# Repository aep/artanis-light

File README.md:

vehicle gps tracker with battery
================================

- cpu:     ESP32
- modem:   Quectel BG96 minipcie
- supply:  ~12V from vehicle
- battery: 2 14500 lifepo cells at 6.4V

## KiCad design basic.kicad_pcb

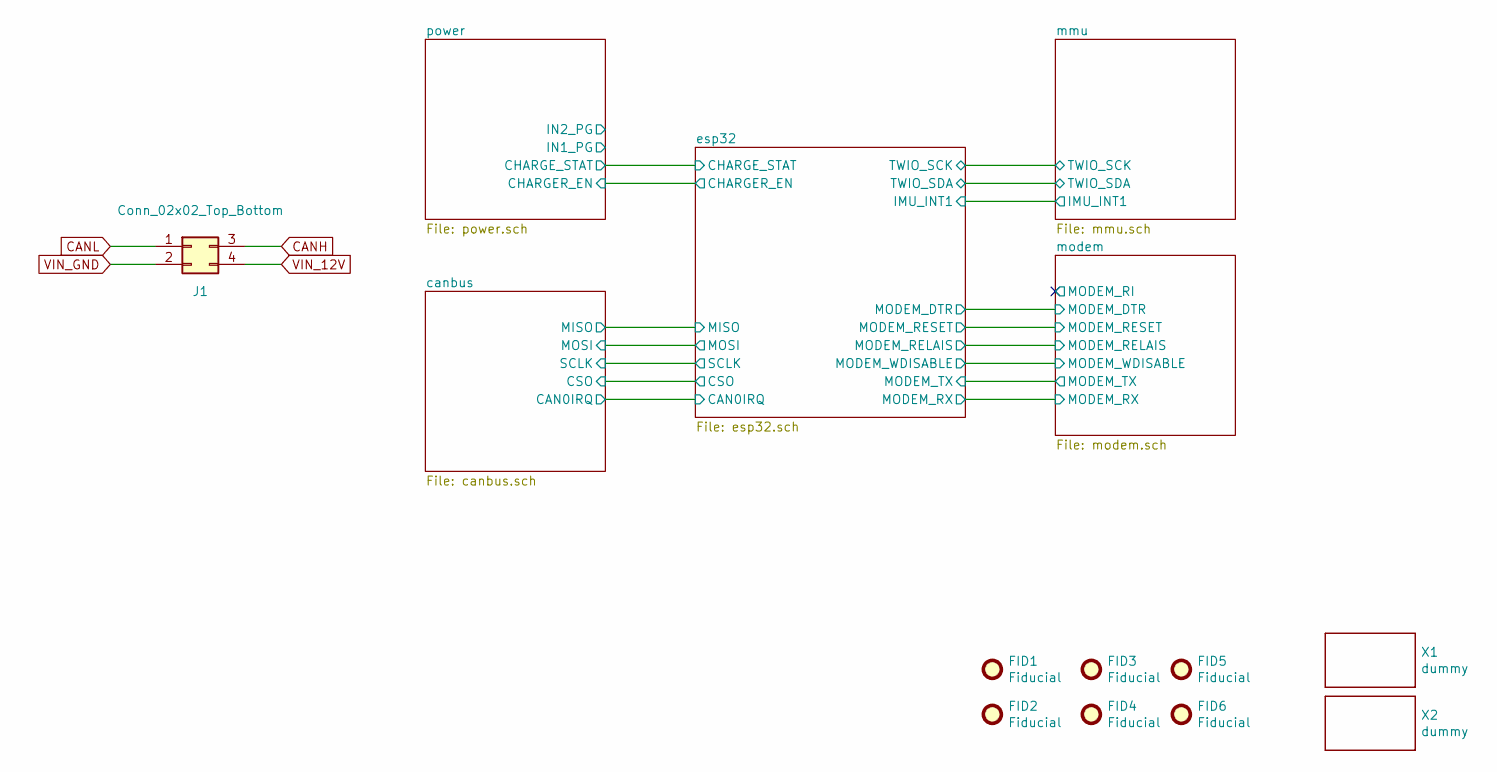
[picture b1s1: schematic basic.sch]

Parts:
FID1, FID2, FID3, FID4, FID5, FID6: Fiducial; FIDUCIAL-1X2
J1: Conn_02x02_Top_Bottom; Molex_Micro-Fit_3.0_43045-0400_2x02_P3.00mm_Horizontal
X1: dummy; WEEE-Logo_2.1x3mm_SilkScreen
X2: dummy; OSHW-LOGO-S

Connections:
CANH: J1.3; also elsewhere on the board
CANL: J1.1; also elsewhere on the board
VIN_12V: J1.4; also elsewhere on the board
VIN_GND: J1.2; also elsewhere on the board

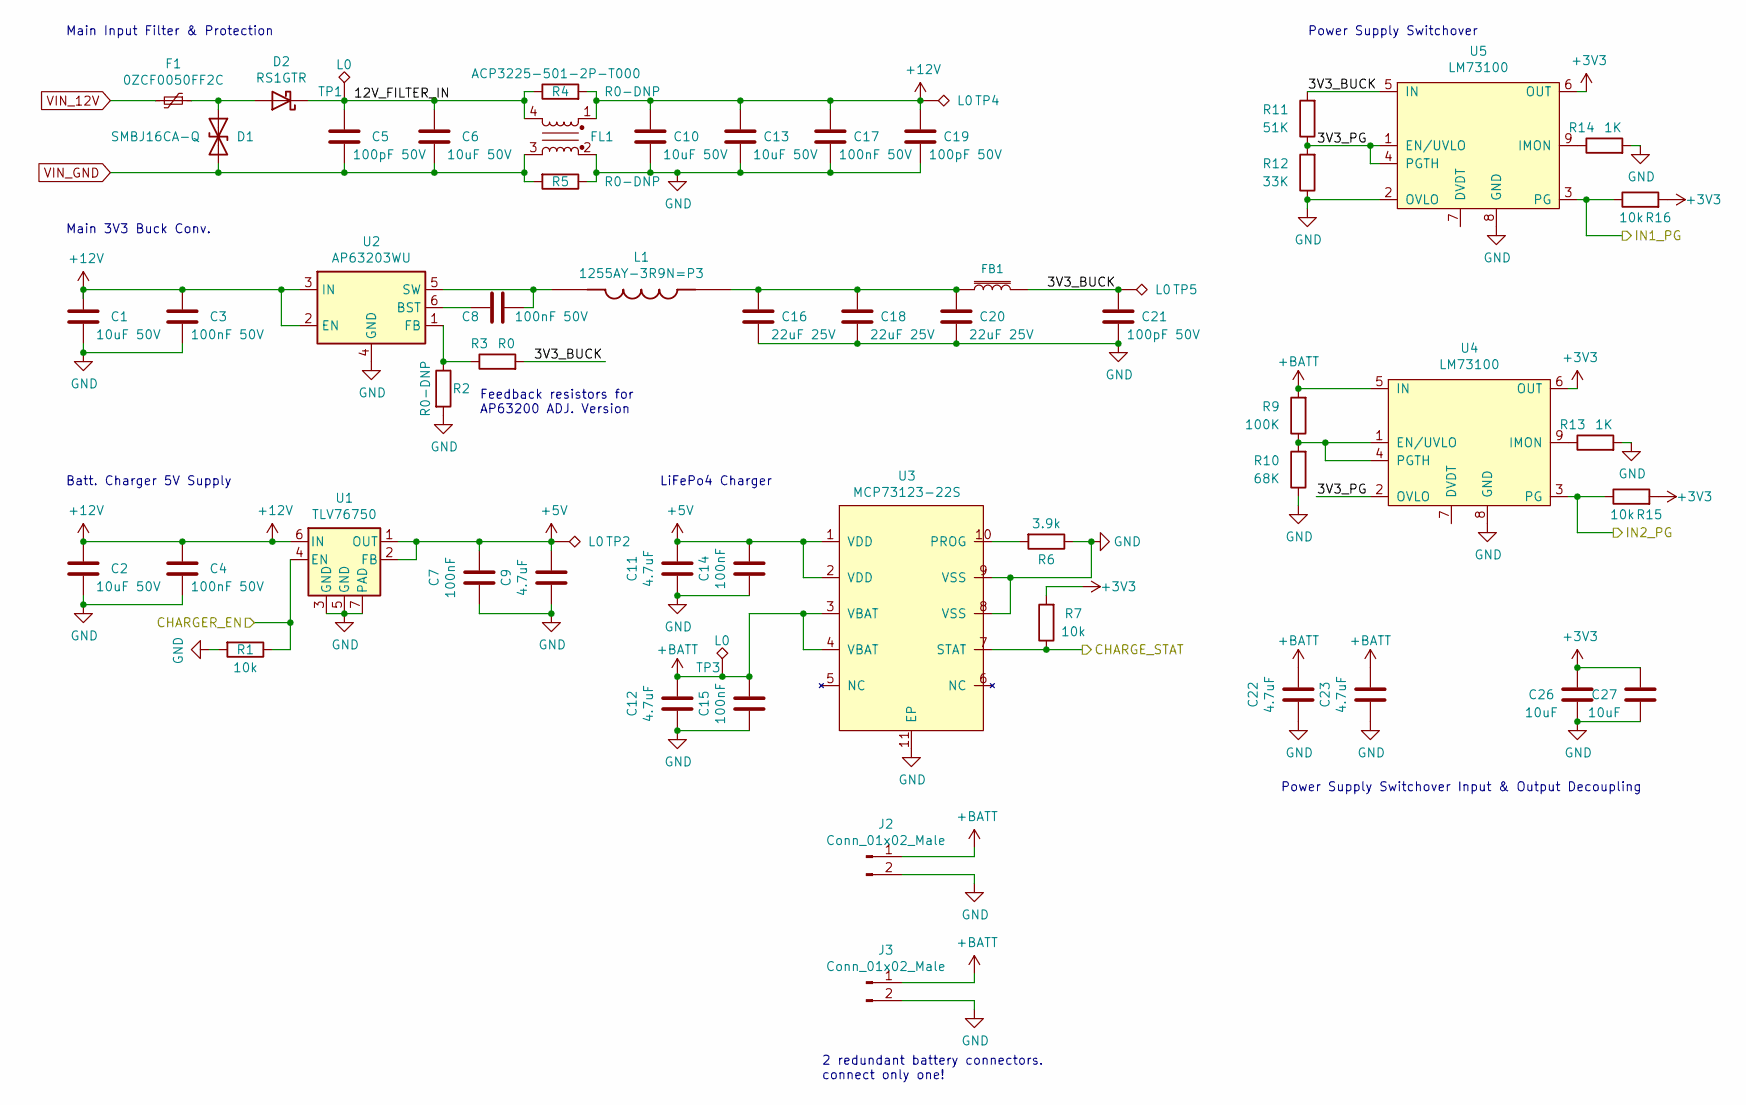
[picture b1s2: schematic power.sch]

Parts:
C1, C2, C6, C10, C13: 10uF 50V; C_0805_2012Metric
C3, C4, C8, C17: 100nF 50V; C_0603_1608Metric
C5, C19, C21: 100pF 50V; C_0603_1608Metric
C7, C14, C15: 100nF; C_0603_1608Metric
C9, C11, C12, C22, C23: 4.7uF; C_0603_1608Metric
C16, C18, C20: 22uF 25V; C_0805_2012Metric
C26, C27: 10uF; C_0603_1608Metric
D1: SMBJ16CA-Q; D_SMB
D2: RS1GTR; D_SMA
F1: 0ZCF0050FF2C; Fuse_2920_7451Metric_Castellated
FB1: BLM18PG181SN1D; 0603
FL1: ACP3225-501-2P-T000; ACP3225
J2: Conn_01x02_Male; JST_SH_BM02B-SRSS-TB_1x02-1MP_P1.00mm_Vertical
J3: Conn_01x02_Male; JST_SH_SM02B-SRSS-TB_1x02-1MP_P1.00mm_Horizontal
L1: 1255AY-3R9N=P3; IND_1255AY-3R9N=P3
R1, R7, R15, R16: 10k; R_0603_1608Metric
R2, R4, R5: R0-DNP; R_0603_1608Metric
R3: R0; R_0603_1608Metric
R6: 3.9k; R_0603_1608Metric
R9: 100K; R_0603_1608Metric
R10: 68K; R_0603_1608Metric
R11: 51K; R_0603_1608Metric
R12: 33K; R_0603_1608Metric
R13, R14: 1K; R_0603_1608Metric
TP1, TP2, TP3, TP4, TP5: L0; TestPoint_Pad_D1.0mm
U1: TLV76750; WSON-6-1EP_2x2mm_P0.65mm_EP1x1.6mm_ThermalVias
U2: AP63203WU; TSOT-23-6
U3: MCP73123-22S; DFN-10-1EP_3x3mm_P0.5mm_EP1.55x2.48mm
U4, U5: LM73100

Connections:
+3V3: C26.1, C27.1, R7.2, R15.2, R16.2, U4.6 (OUT), U5.6 (OUT); also elsewhere on the board
+5V: C7.1, C9.1, C11.1, C14.1, TP2.1, U1.1 (OUT), U1.2 (FB), U3.1 (VDD), U3.2 (VDD)
+12V: C1.2, C2.2, C3.2, C4.2, C10.2, C13.2, C17.2, C19.2, FL1.1, R4.2, TP4.1, U1.6 (IN), U2.2 (EN), U2.3 (IN); also elsewhere on the board
+BATT: C12.1, C15.1, C22.1, C23.1, J2.1, J3.1, R9.2, TP3.1, U3.3 (VBAT), U3.4 (VBAT), U4.5 (IN); also elsewhere on the board
/esp32/CHARGER_EN: R1.1, U1.4 (EN); also elsewhere on the board
/esp32/CHARGE_STAT: R7.1, U3.7 (STAT); also elsewhere on the board
/power/3V3_BUCK: C21.2, FB1.2, R3.2, R11.2, TP5.1, U5.5 (IN)
/power/3V3_PG: R11.1, R12.2, U4.2 (OVLO), U5.1 (EN/UVLO), U5.4 (PGTH)
/power/12V_FILTER_IN: C5.2, C6.2, D2.1 (K), FL1.4, R4.1, TP1.1
/power/IN1_PG: R16.1, U5.3 (PG)
/power/IN2_PG: R15.1, U4.3 (PG)
GND: C1.1, C2.1, C3.1, C4.1, C7.2, C9.2, C10.1, C11.2, C12.2, C13.1, C14.2, C15.2, C16.1, C17.1, C18.1, C19.1, C20.1, C21.1, C22.2, C23.2, C26.2, C27.2, FL1.2, J2.2, J3.2, R1.2, R2.2, R5.1, R6.1, R10.1, R12.1, R13.2, R14.2, U1.3 (GND), U1.5 (GND), U1.7 (PAD), U2.4 (GND), U3.8 (VSS), U3.9 (VSS), U3.11 (EP), U4.8 (GND), U5.2 (OVLO), U5.8 (GND); also elsewhere on the board
unnamed: C8.1, L1.1, U2.5 (SW)
unnamed: C8.2, U2.6 (BST)
unnamed: C16.2, C18.2, C20.2, FB1.1, L1.2
unnamed: D1.1 (A1), D2.2 (A), F1.1
unnamed: R2.1, R3.1, U2.1 (FB)
unnamed: R6.2, U3.10 (PROG)
unnamed: R9.1, R10.2, U4.1 (EN/UVLO), U4.4 (PGTH)
unnamed: R13.1, U4.9 (IMON)
unnamed: R14.1, U5.9 (IMON)
VIN_12V: F1.2; also elsewhere on the board
VIN_GND: C5.1, C6.1, D1.2 (A2), FL1.3, R5.2; also elsewhere on the board

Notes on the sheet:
Feedback resistors for AP63200 ADJ. Version
2 redundant battery connectors. connect only one!
Power Supply Switchover
Batt. Charger 5V Supply
LiFePo4 Charger
Main 3V3 Buck Conv.
Main Input Filter & Protection
Power Supply Switchover Input & Output Decoupling

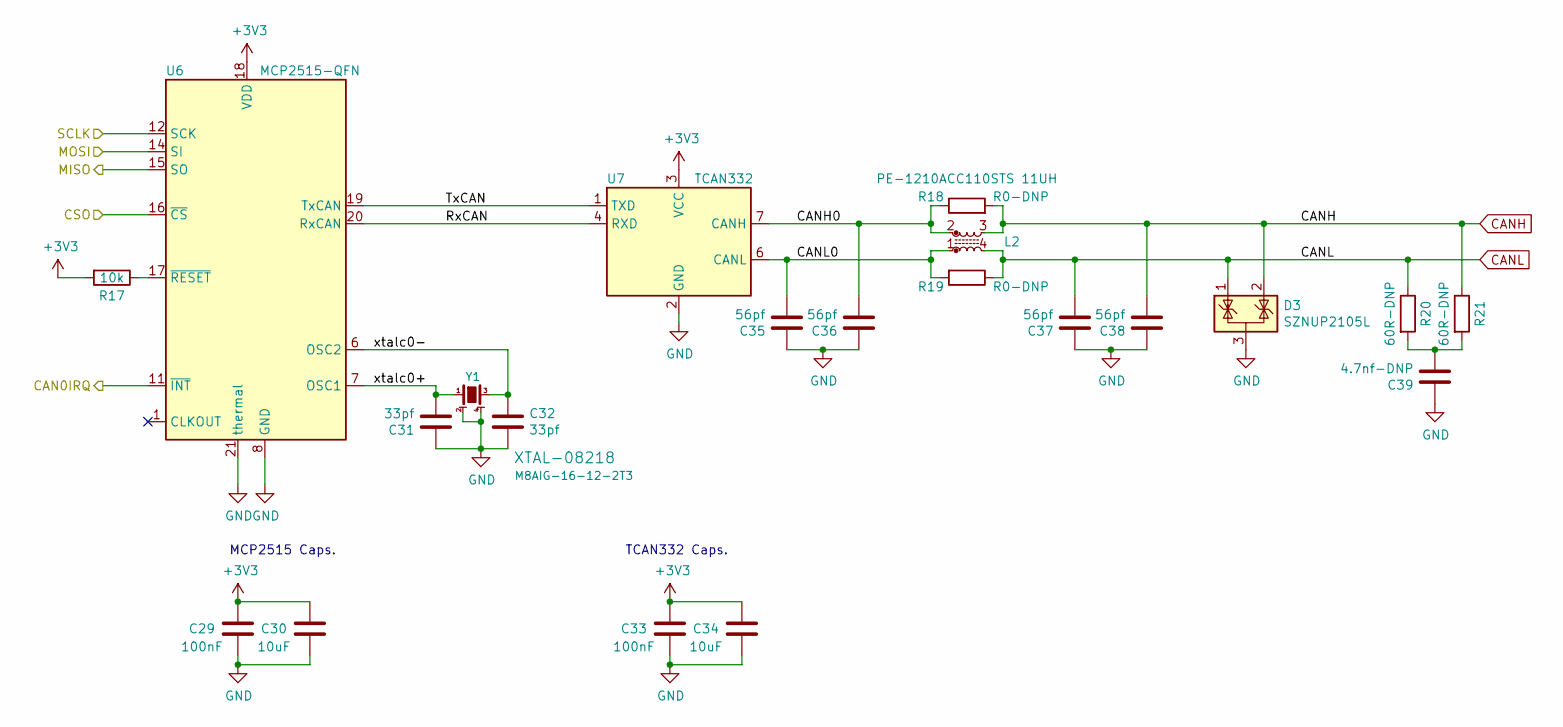
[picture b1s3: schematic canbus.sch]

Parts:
C29, C33: 100nF; C_0603_1608Metric
C30, C34: 10uF; C_0603_1608Metric
C31, C32: 33pf; C_0603_1608Metric
C35, C36, C37, C38: 56pf; C_0603_1608Metric
C39: 4.7nf-DNP; C_0603_1608Metric
D3: SZNUP2105L; SOT-23
L2: PE-1210ACC110STS 11UH; PE-1210ACC
R17: 10k; R_0603_1608Metric
R18, R19: R0-DNP; R_0603_1608Metric
R20, R21: 60R-DNP; R_0603_1608Metric
U6: MCP2515-QFN; QFN-20-1EP_4x4mm_P0.5mm_EP2.5x2.5mm_ThermalVias
U7: TCAN332; SOT-23-8
Y1: M8AIG-16-12-2T3; Crystal_SMD_Abracon_ABM8G-4Pin_3.2x2.5mm

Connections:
+3V3: C29.1, C30.1, C33.1, C34.1, R17.2, U6.18 (VDD), U7.3 (VCC); also elsewhere on the board
/canbus/CAN0IRQ: U6.11 (~INT); also elsewhere on the board
/canbus/CANH0: C36.2, L2.2, R18.1, U7.7 (CANH)
/canbus/CANL0: C35.2, L2.1, R19.2, U7.6 (CANL)
/canbus/CSO: U6.16 (~CS); also elsewhere on the board
/canbus/MISO: U6.15 (SO); also elsewhere on the board
/canbus/MOSI: U6.14 (SI); also elsewhere on the board
/canbus/RxCAN: U6.20 (RxCAN), U7.4 (RXD)
/canbus/SCLK: U6.12 (SCK); also elsewhere on the board
/canbus/TxCAN: U6.19 (TxCAN), U7.1 (TXD)
/canbus/xtalc0+: C31.2, U6.7 (OSC1), Y1.1
/canbus/xtalc0-: C32.1, U6.6 (OSC2), Y1.3
CANH: C38.2, D3.2 (K), L2.3, R18.2, R21.1; also elsewhere on the board
CANL: C37.2, D3.1 (K), L2.4, R19.1, R20.1; also elsewhere on the board
GND: C29.2, C30.2, C31.1, C32.2, C33.2, C34.2, C35.1, C36.1, C37.1, C38.1, C39.1, D3.3 (A), U6.8 (GND), U6.21 (thermal), U7.2 (GND), Y1.2, Y1.4; also elsewhere on the board
unnamed: C39.2, R20.2, R21.2
unnamed: R17.1, U6.17 (~RESET)

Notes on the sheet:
MCP2515 Caps.
TCAN332 Caps.

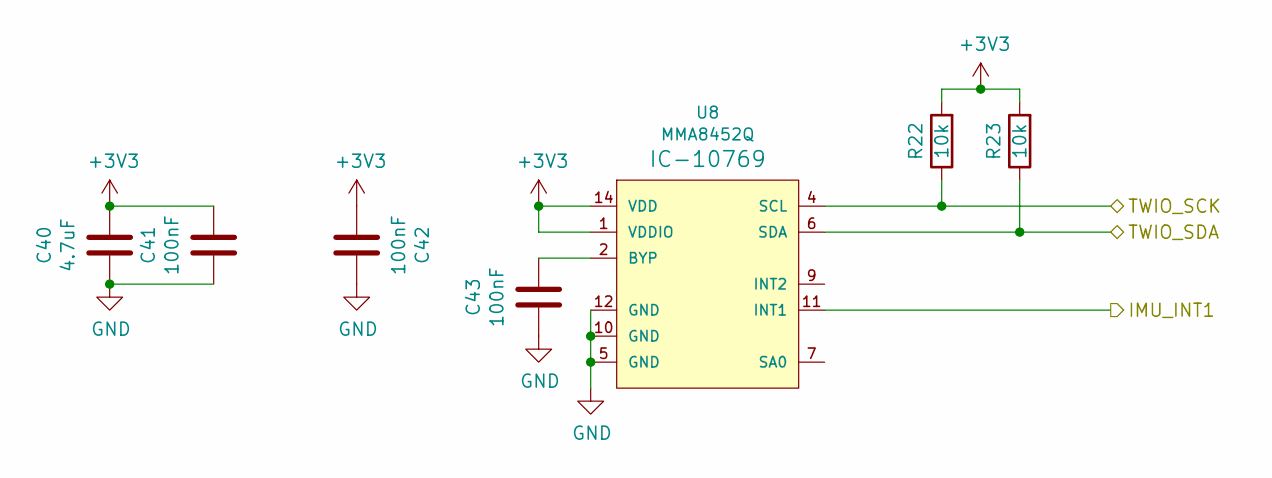
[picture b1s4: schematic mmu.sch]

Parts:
C40: 4.7uF; C_0603_1608Metric
C41, C42, C43: 100nF; C_0603_1608Metric
R22, R23: 10k; R_0603_1608Metric
U8: MMA8452Q; QFN-16

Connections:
+3V3: C40.1, C41.1, C42.2, R22.2, R23.2, U8.1 (VDDIO), U8.14 (VDD); also elsewhere on the board
/esp32/IMU_INT1: U8.11 (INT1); also elsewhere on the board
/esp32/TWIO_SCK: R22.1, U8.4 (SCL); also elsewhere on the board
/esp32/TWIO_SDA: R23.1, U8.6 (SDA); also elsewhere on the board
GND: C40.2, C41.2, C42.1, C43.2, U8.5 (GND), U8.10 (GND), U8.12 (GND); also elsewhere on the board
unnamed: C43.1, U8.2 (BYP)

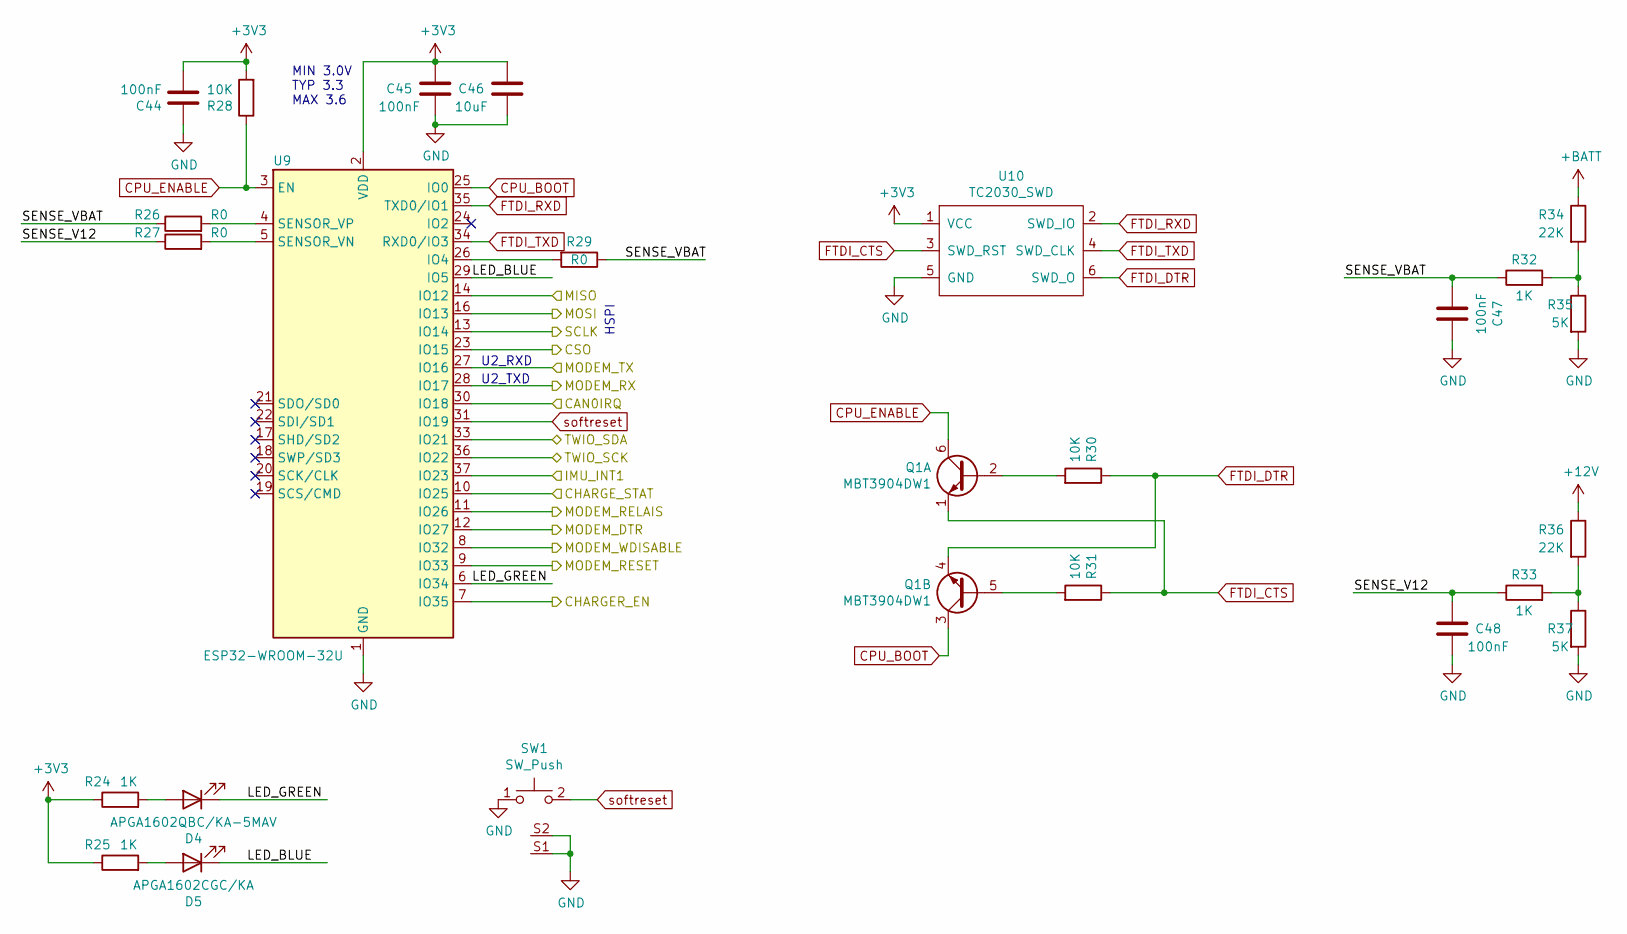
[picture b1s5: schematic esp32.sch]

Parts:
C44: 100nF; 0603
C45, C47, C48: 100nF; C_0603_1608Metric
C46: 10uF; C_0603_1608Metric
D4: APGA1602QBC/KA-5MAV; LED_0603_1608Metric
D5: APGA1602CGC/KA; LED_0603_1608Metric
Q1: MBT3904DW1; SOT-363_SC-70-6
R24, R25, R32, R33: 1K; R_0603_1608Metric
R26, R27, R29: R0; R_0603_1608Metric
R28, R30, R31: 10K; R_0603_1608Metric
R34, R36: 22K; R_0603_1608Metric
R35, R37: 5K; R_0603_1608Metric
SW1: SW_Push; SW_1825027-5
U9: ESP32-WROOM-32U
U10: TC2030_SWD; Tag-Connect_TC2030-IDC-FP_2x03_P1.27mm_Vertical

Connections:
+3V3: C44.2, C45.1, C46.1, R24.1, R25.1, R28.2, U9.2 (VDD), U10.1 (VCC); also elsewhere on the board
+12V: R36.1; also elsewhere on the board
+BATT: R34.1; also elsewhere on the board
/canbus/CAN0IRQ: U9.30 (IO18); also elsewhere on the board
/canbus/CSO: U9.23 (IO15); also elsewhere on the board
/canbus/MISO: U9.14 (IO12); also elsewhere on the board
/canbus/MOSI: U9.16 (IO13); also elsewhere on the board
/canbus/SCLK: U9.13 (IO14); also elsewhere on the board
/esp32/CHARGER_EN: U9.7 (IO35); also elsewhere on the board
/esp32/CHARGE_STAT: U9.10 (IO25); also elsewhere on the board
/esp32/IMU_INT1: U9.37 (IO23); also elsewhere on the board
/esp32/LED_BLUE: D5.1 (K), U9.29 (IO5)
/esp32/LED_GREEN: D4.1 (K), U9.6 (IO34)
/esp32/MODEM_DTR: U9.12 (IO27); also elsewhere on the board
/esp32/MODEM_RELAIS: U9.11 (IO26); also elsewhere on the board
/esp32/MODEM_RESET: U9.9 (IO33); also elsewhere on the board
/esp32/MODEM_RX: U9.28 (IO17); also elsewhere on the board
/esp32/MODEM_TX: U9.27 (IO16); also elsewhere on the board
/esp32/MODEM_WDISABLE: U9.8 (IO32); also elsewhere on the board
/esp32/SENSE_V12: C48.2, R27.1, R33.1
/esp32/SENSE_VBAT: C47.2, R26.1, R29.1, R32.1
/esp32/TWIO_SCK: U9.36 (IO22); also elsewhere on the board
/esp32/TWIO_SDA: U9.33 (IO21); also elsewhere on the board
CPU_BOOT: Q1.3 (C2), U9.25 (IO0)
CPU_ENABLE: Q1.6 (C1), R28.1, U9.3 (EN)
FTDI_CTS: Q1.1 (E1), R31.1, U10.3 (SWD_RST)
FTDI_DTR: Q1.4 (E2), R30.1, U10.6 (SWD_O)
FTDI_RXD: U9.35 (TXD0/IO1), U10.2 (SWD_IO)
FTDI_TXD: U9.34 (RXD0/IO3), U10.4 (SWD_CLK)
GND: C44.1, C45.2, C46.2, C47.1, C48.1, R35.2, R37.2, SW1.1, SW1.S1 (Shield1), SW1.S2 (Shield2), U9.1 (GND), U9.15 (GND), U9.38 (GND), U9.39 (GND), U10.5 (GND); also elsewhere on the board
unnamed: D4.2 (A), R24.2
unnamed: D5.2 (A), R25.2
unnamed: Q1.2 (B1), R30.2
unnamed: Q1.5 (B2), R31.2
unnamed: R26.2, U9.4 (SENSOR_VP)
unnamed: R27.2, U9.5 (SENSOR_VN)
unnamed: R29.2, U9.26 (IO4)
unnamed: R32.2, R34.2, R35.1
unnamed: R33.2, R36.2, R37.1
softreset: SW1.2, U9.31 (IO19)

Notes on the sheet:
MIN 3.0V TYP 3.3 MAX 3.6
HSPI
U2_RXD
U2_TXD

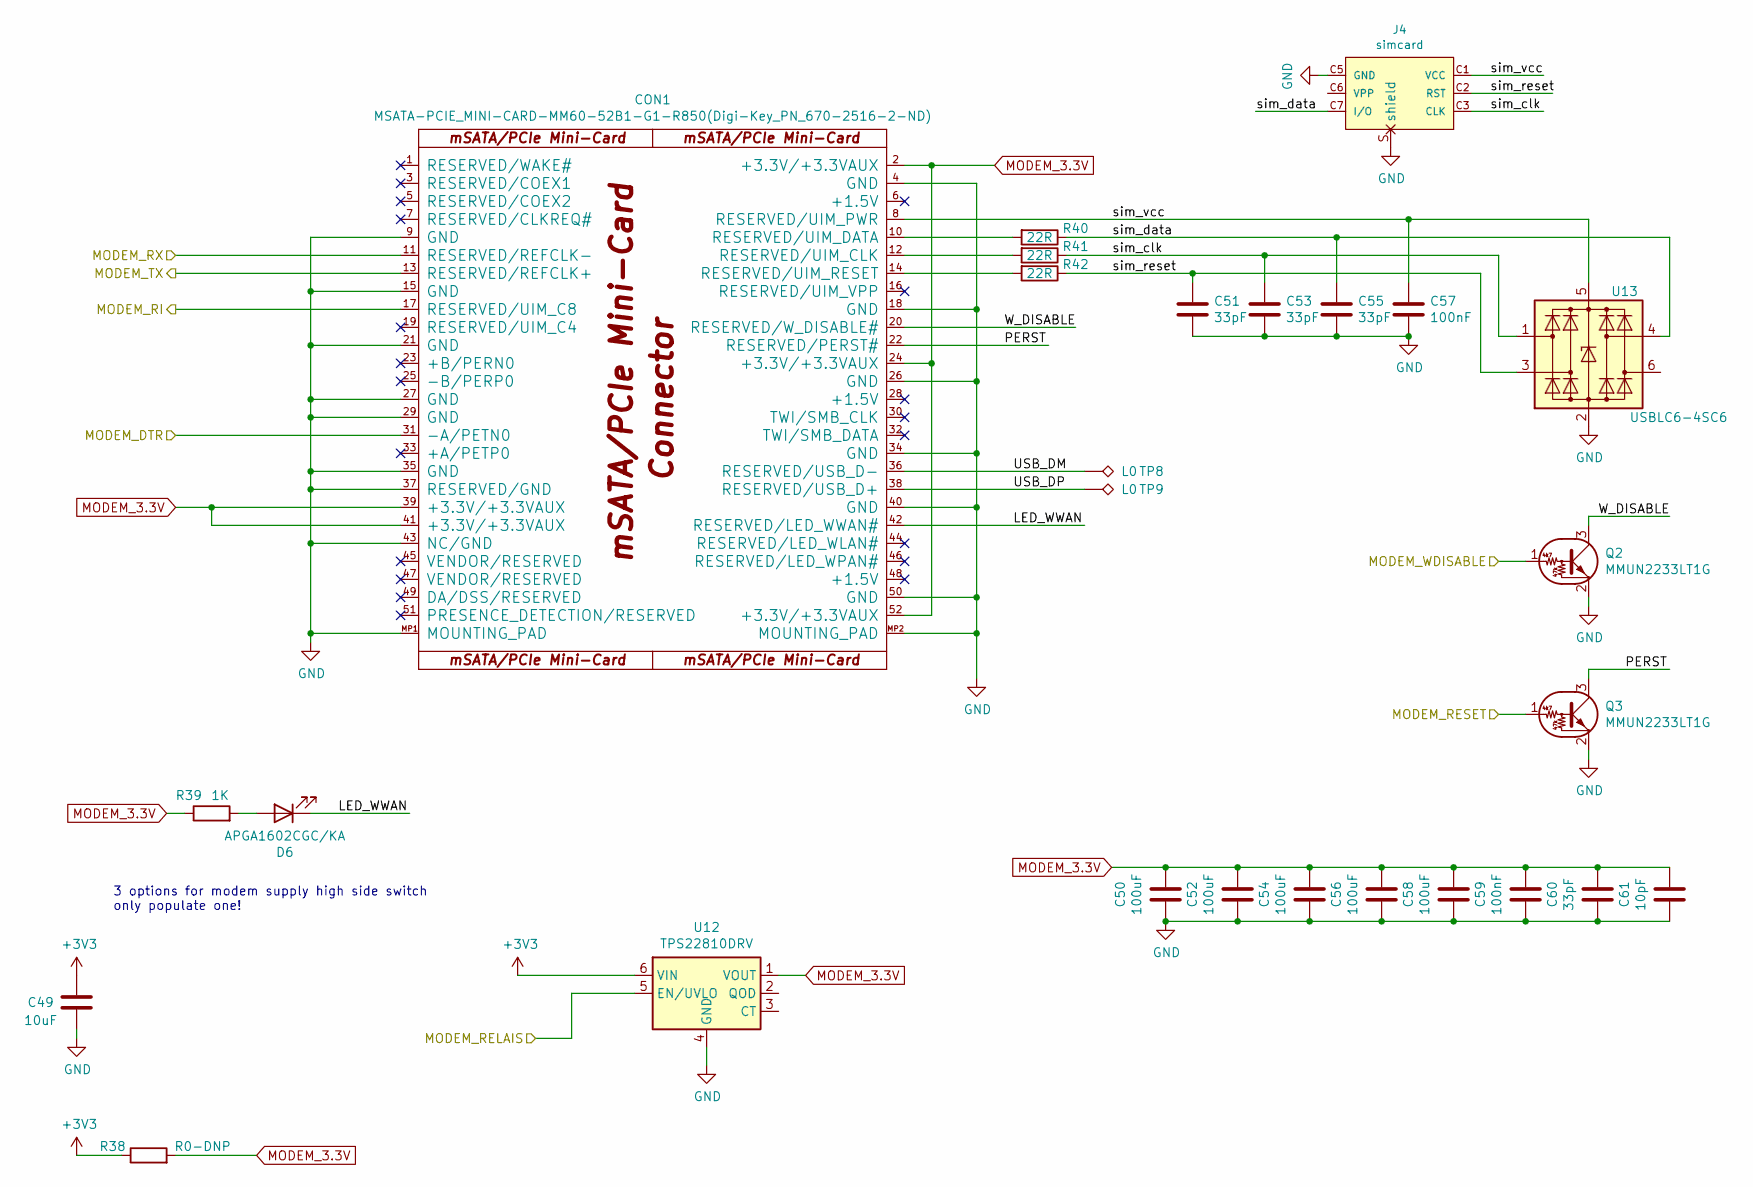
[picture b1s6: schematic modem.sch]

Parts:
C49: 10uF; C_0603_1608Metric
C50, C52, C54, C56, C58: 100uF; C_1206_3216Metric
C51, C53, C55, C60: 33pF; C_0603_1608Metric
C57, C59: 100nF; C_0603_1608Metric
C61: 10pF; C_0603_1608Metric
CON1: MSATA-PCIE_MINI-CARD-MM60-52B1-G1-R850(Digi-Key_P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; MM60-52B1-G1-R850
D6: APGA1602CGC/KA; LED_0603_1608Metric
J4: simcard; nanosim-Wurth-693043020611
Q2, Q3: MMUN2233LT1G; SOT-23
R38: R0-DNP; R_0603_1608Metric
R39: 1K; R_0603_1608Metric
R40, R41, R42: 22R; R_0603_1608Metric
TP8, TP9: L0; TestPoint_Pad_D1.0mm
U12: TPS22810DRV; WSON-6-1EP_2x2mm_P0.65mm_EP1x1.6mm
U13: USBLC6-4SC6; SOT-23-6

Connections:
+3V3: C49.1, R38.1, U12.6 (VIN); also elsewhere on the board
/esp32/MODEM_DTR: CON1.31 (-A/PETN0); also elsewhere on the board
/esp32/MODEM_RELAIS: U12.5 (EN/UVLO); also elsewhere on the board
/esp32/MODEM_RESET: Q3.1 (B); also elsewhere on the board
/esp32/MODEM_RX: CON1.11 (RESERVED/REFCLK-); also elsewhere on the board
/esp32/MODEM_TX: CON1.13 (RESERVED/REFCLK+); also elsewhere on the board
/esp32/MODEM_WDISABLE: Q2.1 (B); also elsewhere on the board
/modem/LED_WWAN: CON1.42 (RESERVED/LED_WWAN#), D6.1 (K)
/modem/MODEM_RI: CON1.17 (RESERVED/UIM_C8)
/modem/PERST: CON1.22 (RESERVED/PERST#), Q3.3 (C)
/modem/USB_DM: CON1.36 (RESERVED/USB_D-), TP8.1
/modem/USB_DP: CON1.38 (RESERVED/USB_D+), TP9.1
/modem/W_DISABLE: CON1.20 (RESERVED/W_DISABLE#), Q2.3 (C)
/modem/sim_clk: C53.1, J4.C3 (CLK), R41.1, U13.1 (I/O1)
/modem/sim_data: C55.1, J4.C7 (I/O), R40.1, U13.4 (I/O3)
/modem/sim_reset: C51.1, J4.C2 (RST), R42.1, U13.3 (I/O2)
/modem/sim_vcc: C57.1, CON1.8 (RESERVED/UIM_PWR), J4.C1 (VCC), U13.5 (VBUS)
GND: C49.2, C50.2, C51.2, C52.2, C53.2, C54.2, C55.2, C56.2, C57.2, C58.2, C59.2, C60.2, C61.2, CON1.4 (GND), CON1.9 (GND), CON1.15 (GND), CON1.18 (GND), CON1.21 (GND), CON1.26 (GND), CON1.27 (GND), CON1.29 (GND), CON1.34 (GND), CON1.35 (GND), CON1.37 (RESERVED/GND), CON1.40 (GND), CON1.43 (NC/GND), CON1.50 (GND), CON1.MP1 (MOUNTING_PAD), CON1.MP2 (MOUNTING_PAD), J4.C5 (GND), J4.S (shield), Q2.2 (E), Q3.2 (E), U12.4 (GND), U12.7 (GND), U13.2 (GND); also elsewhere on the board
MODEM_3.3V: C50.1, C52.1, C54.1, C56.1, C58.1, C59.1, C60.1, C61.1, CON1.2 (+3.3V/+3.3VAUX), CON1.24 (+3.3V/+3.3VAUX), CON1.39 (+3.3V/+3.3VAUX), CON1.41 (+3.3V/+3.3VAUX), CON1.52 (+3.3V/+3.3VAUX), R38.2, R39.1, U12.1 (VOUT)
unnamed: CON1.10 (RESERVED/UIM_DATA), R40.2
unnamed: CON1.12 (RESERVED/UIM_CLK), R41.2
unnamed: CON1.14 (RESERVED/UIM_RESET), R42.2
unnamed: D6.2 (A), R39.2

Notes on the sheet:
3 options for modem supply high side switch only populate one!

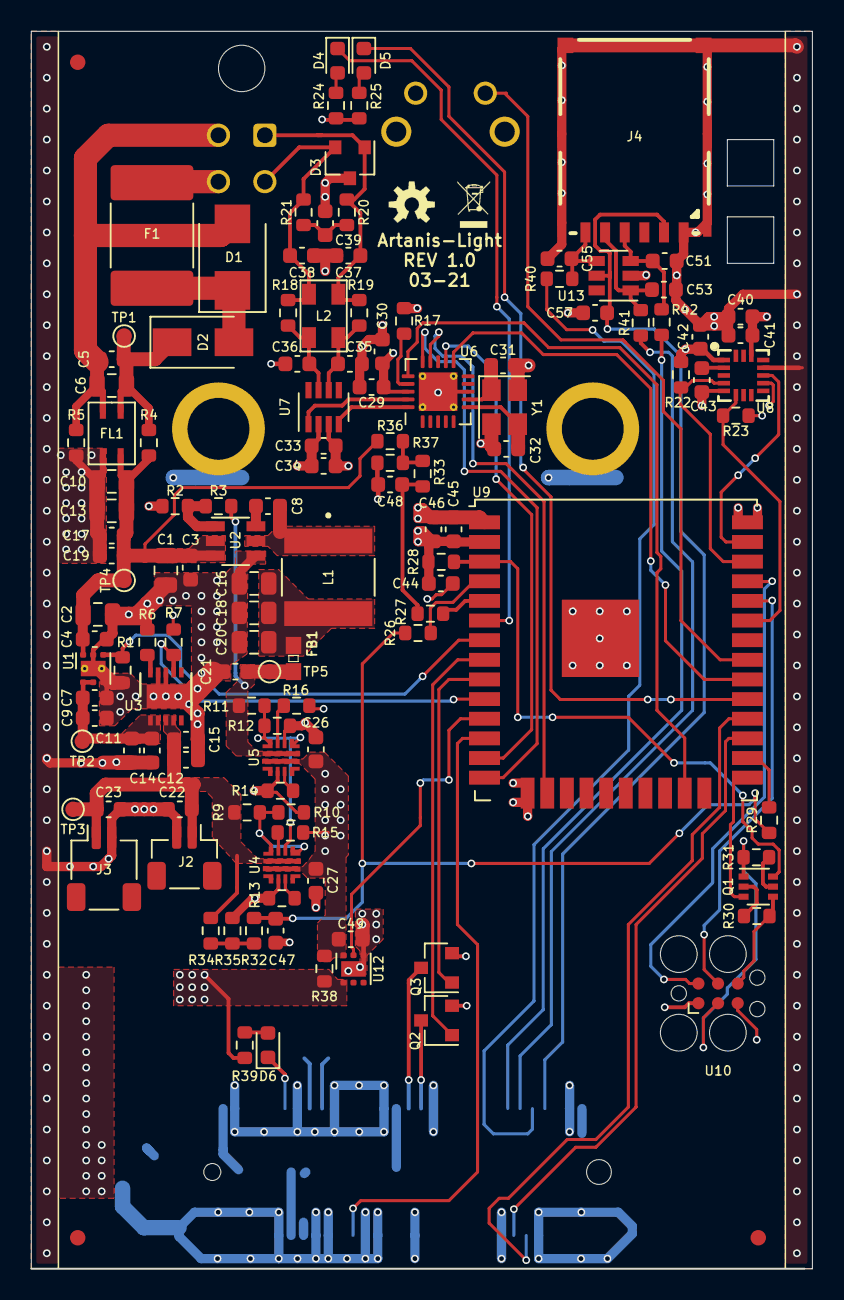
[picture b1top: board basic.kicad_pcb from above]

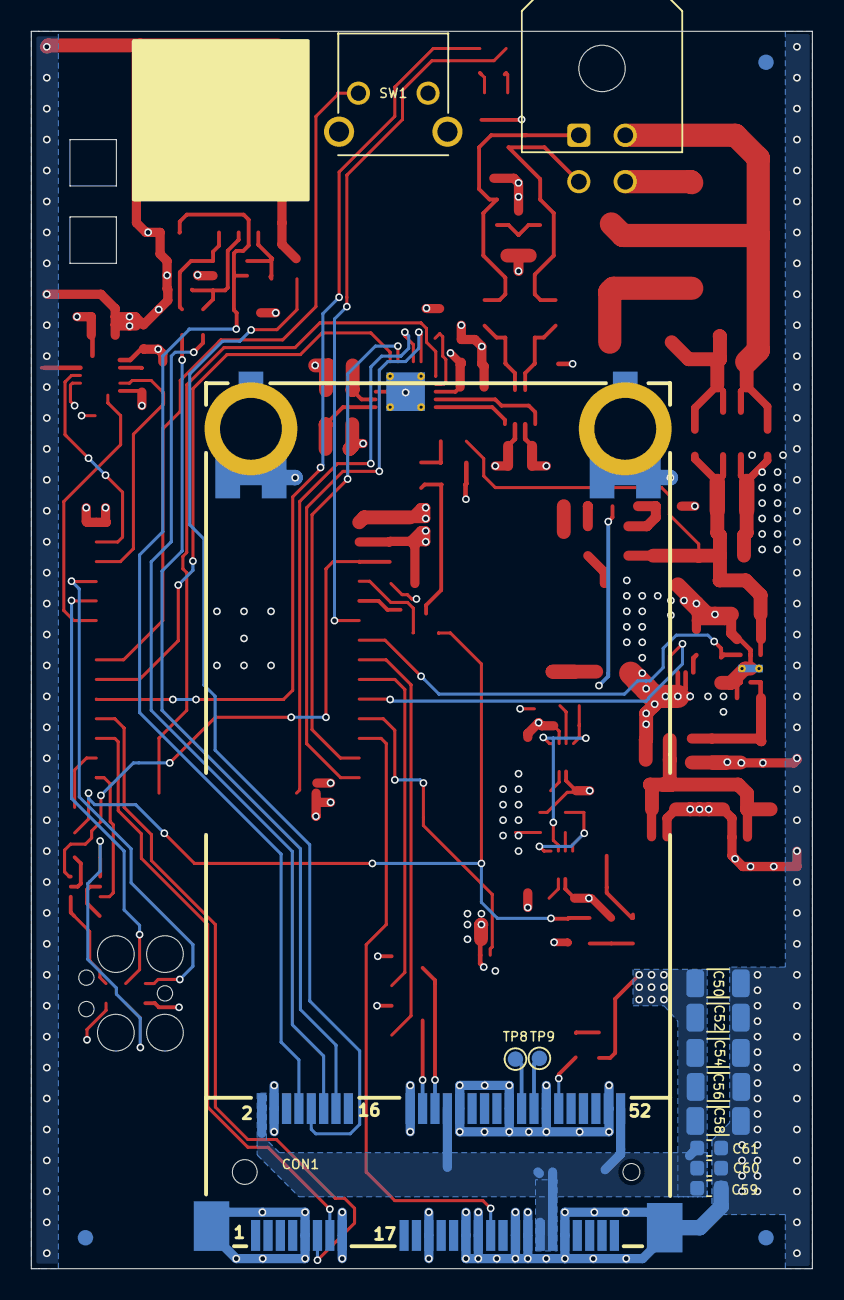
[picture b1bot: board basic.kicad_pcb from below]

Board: 4 copper layers, 50.5 x 80.0 mm, 147 parts (16 on the bottom side), 82 nets.

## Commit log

2021-02-24 init
2021-02-24 readability
2021-02-27 Updated docs.
2021-02-27 MMU Schematic rework.
2021-02-28 Esp32 & Canbus Sch. edited.
2021-02-28 Modem schematic updated.
2021-02-28 Power Sch. Updated.
2021-03-01 Fixed Buck feedback reference.
2021-03-01 Added LM73100 to project library.
2021-03-02 Updated power mux with LM73100.
2021-03-06 Changed PTC Fuse.
2021-03-10 Power section placement completed.
2021-03-11 Power section routing completed.
2021-03-17 PCB design updated.
2021-03-17 PCB Design completed.
2021-03-17 Fixed DRC Errors.
2021-03-18 Changed MCU connection.
2021-03-20 Added cutout for antenna cable.
2021-03-20 Added battery holder PCB and Created 3D model for enclosure.
2021-03-20 Added 3D model and DXF for enclousure.
